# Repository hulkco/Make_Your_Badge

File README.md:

# Crea tu Badge con Kicad
## Objetivo

>**Crear una tarjeta de circuito impreso de forma personalizada, usando herramientas Open Source.**

## Dirigido a:

>**Cualquier persona que esté interesada en crear tarjetas de circuito impreso, no es necesario tener conocimientos alguno de electrónica o previos en diseño de tarjetas, ya que el contenido va enfocado al uso de las herramientas.**

## Software requerido.

* [Kicad](http://kicad-pcb.org/) 
- [LibreCAD](https://librecad.org/) 
+ [InkScape](https://inkscape.org/) 
* [SVG2Mod](https://github.com/mtl/svg2mod) (Este script usa Python [2.7](https://www.python.org/downloads/release/python-2716/), tenerlo en cuenta) 

>**Nota.- Yo usare Linux (Distribución Linux Mint), si usas otro sistema operativo, no te preocupes, todo el software que se necesita al ser open source, tiene versiones para Linux, MacOSX y Windows.**

## Contenido

0. Que es un Badge electrónico.
1. Herramientas a usar.
2. Selección de la forma de la PCB.
3. Diseño de la forma.
4. Exportar a kicad.
5. Diseño de un circuito básico.
6. Asignación de huellas.
7. Asignación de modelos 3d.
8. Render final del Badge en 3d.
9. Sugerencias para fabricación de la PCB

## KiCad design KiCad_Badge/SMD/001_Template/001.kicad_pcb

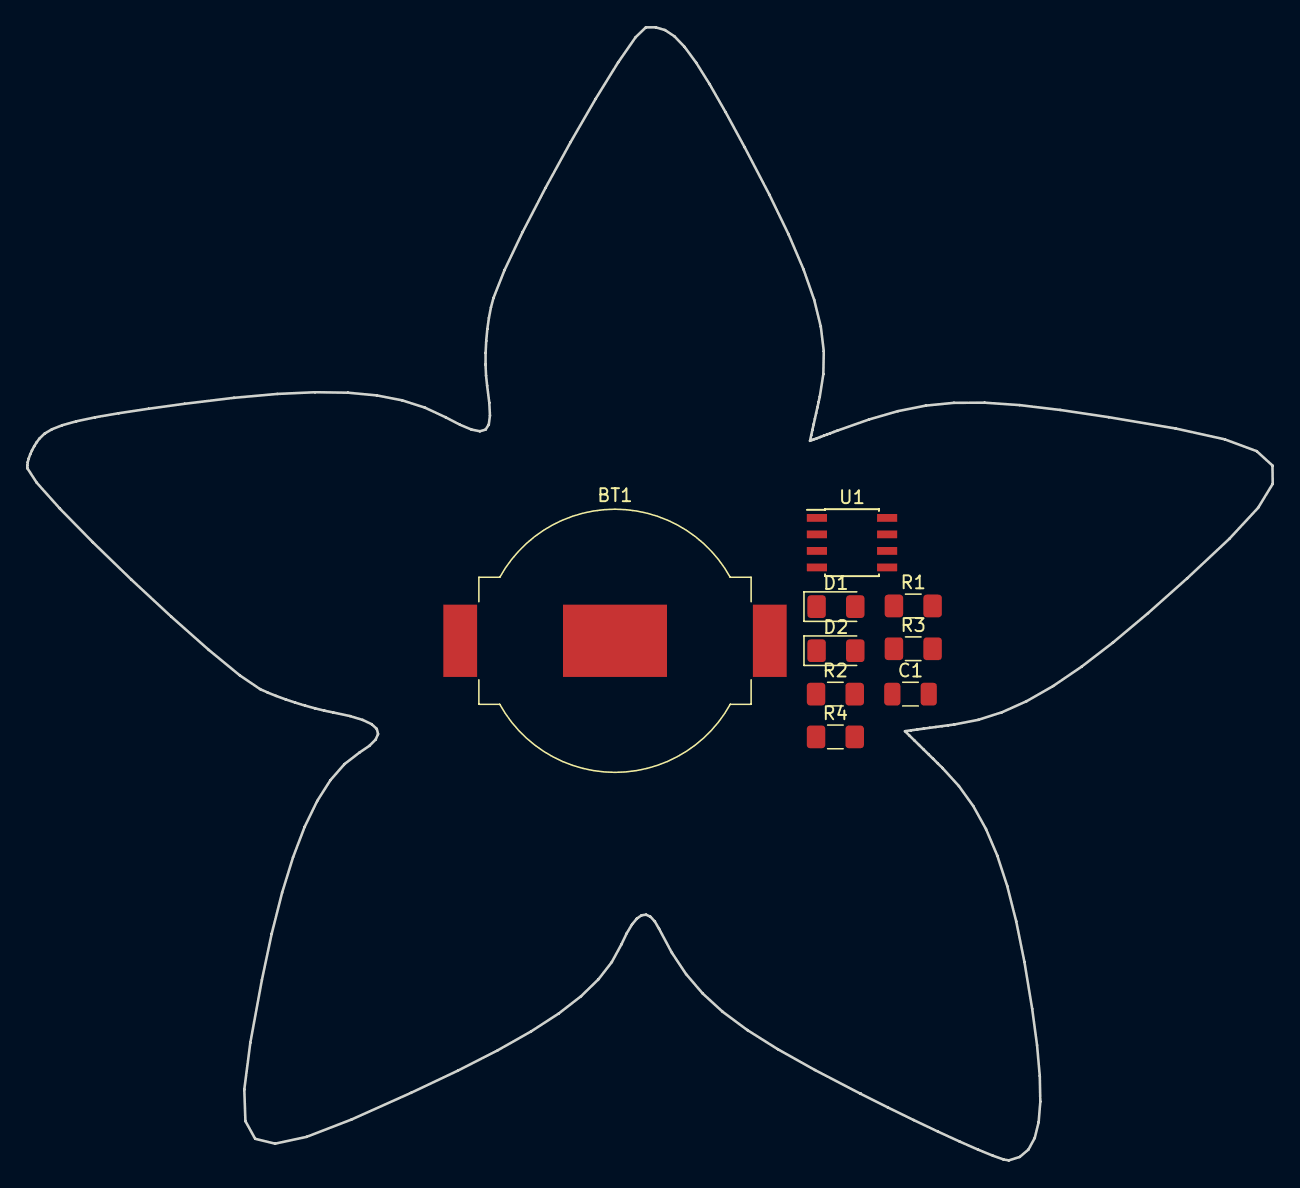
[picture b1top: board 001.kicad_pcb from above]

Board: 2 copper layers, 95.8 x 87.2 mm, 9 parts (0 on the bottom side), 7 nets, no tracks yet.

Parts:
BT1: Battery_Cell; BatteryHolder_MPD_BC2003_1x2032
C1: 10uF; C_1206_3216Metric
D1, D2: LED; LED_1206_3216Metric_Pad1.42x1.75mm_HandSolder
R1, R3, R4: 1k; R_1206_3216Metric_Pad1.42x1.75mm_HandSolder
R2: 10k; R_1206_3216Metric_Pad1.42x1.75mm_HandSolder
U1: LM555; SOIC-8_3.9x4.9mm_P1.27mm

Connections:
+3V3: BT1.1, R1.1, R3.1, U1.4, U1.8
GND: BT1.2, C1.1, R4.2, U1.1
unnamed: C1.2, R2.2, U1.2, U1.6
unnamed: D1.1, D2.2, U1.3
unnamed: D1.2, R3.2
unnamed: D2.1, R4.1
unnamed: R1.2, R2.1, U1.7

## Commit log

2019-04-21 Create Repo
2019-04-22 Update Footprints and Template
2019-04-22 Add image
2019-04-27 Some minor updates 26-03-2019
2019-05-09 Update content.
2019-05-09 Update content
2019-05-13 Minor updates
2019-05-15 Update Directory source of images
